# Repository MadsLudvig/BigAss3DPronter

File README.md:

# Industrial 3D Printer
*__Big 3D printer made with industrial parts from an injection molding machine__*

### Introduction

This is a 3D printer made with an extruder from an injection moulding machine and Motors and axis from several old ATM CNC robots. It will be using an material dryer and a mini vacuum conveyor for supplying the extruder with material. It will be build such that the extruder only moves on one axis because of its weight (approximately 50kg). The extruder will be moved on the x-axis and the bottom plate will be moved on the z- and y-axis. The software will be Marlin which is going to run on a Teensy 4.0. Then octoprint will be used as an Marlin host to control. Here octoprint will run on a Raspberry Pi 4.0 with an 15" industrial grade touch screen.

*__More information on the individual modules can be seen in the "Modules" folder__*

### Mechanical composition

Here as said before the extruder is going to be moved in the X-axis and the bottom plate is going to be moved in the Y- and Z-axis. This is seen in Figure 5 below:

*Figure 5: Here is seen an example of how the axis will look*

Here it should be noted that although the axis placements are correct on the image. The way the axisses are moved are not. This image is just to show axis placement. The Z-axis is not moving the extruder it should here be moving the bottom plate instead. The reason why the extruder is placed on the x-axis is because of its sheer size and weight. Here it will be advantagous only to move it from side to side to minimize movement of mass. To make the x-axis move the weight of the extruder, the long axis of the ATM CNC robot is going to be used. This is because this has lots of already built-in support and can therefore support the extruder with ease. It also has place for motor mounting, gear and gearrack for moving the axis, and a cable carrier. This i going to be very advantageus for running the material supply line for the extruder, motor cables for x and w axisses, and heating element wires for extruder. Everything will then be mounted on a steel frame made out of welded steel beams. The material of the bottom plate is being researched, so the best material can be found. For now the material is aluminium, but that could also be replaced with borosilicate glass because of its hardness and temperature resistance

### Global Bill of Materials

| Name                                         | Quantity |                             Link                             | Price (DKK) |
| :------------------------------------------- | :------: | :----------------------------------------------------------: | :---------: |
| Conradt mini vacuum conveyer                 |    1     |                                                              |    4000     |
| ILCE-QX1 Power adapter                       |    1     | [Link](https://www.subtel.dk/index.php?cl=details&offerId=3978956963&lang=6&anid=915664&cnid=192d2e4a1f71bd07ce1a5f9bbb185e09&campaign=dk-pla/Netzteil/915664&gclid=Cj0KCQiAs5eCBhCBARIsAEhk4r6M4nEBqRl9llAmq8cqiiVEmtkUiZZ6ZFrAzY_FEcEVpPGQpeQw50saAnzREALw_wcB) |     259     |
| 15" Touch screen                             |    1     | [Link](https://www.beetronics.dk/15-tommer-touchskaerm-metal-4-3) |    2699     |
| Cable                                        |    1     |   [Link](https://dk.rs-online.com/web/p/yy-kabel/1811780/)   |     589     |
| Connector                                    |    16    |  [Link](https://dk.rs-online.com/web/p/d-sub-stik/5443749/)  |    6.376    |
| Connector house                              |    16    | [Link](https://dk.rs-online.com/web/p/d-sub-bagkapper/5444039/) |    27.22    |
| Material dryer                               |    1     |                                                              |     NaN     |
| SN74LS640N                                   |    6     | [Link](https://www.ti.com/store/ti/en/p/product/?p=SN74LS640N) |    9.54     |
| SN74ABT245BN                                 |    6     | [Link](https://www.ti.com/store/ti/en/p/product/?p=SN74ABT245BN) |    4.52     |
| Aluminium bottom plate                       |    1     |                                                              |     NaN     |
| Heating elements bottom plate                |    1     |                                                              |     NaN     |
| Steel frame                                  |    1     |                                                              |     NaN     |
| Mounting adapter for servo motor to extruder |    1     |                                                              |     NaN     |

So here the price comes up to: 8169kr. DKK for now. Here it should be noted that this is not close to the final cost, since the mounting brackets, the steel frame, and the aluminium bottom plate will cost a lot.

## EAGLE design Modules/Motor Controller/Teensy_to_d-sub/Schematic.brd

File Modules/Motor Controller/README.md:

# Motor Controller
The motors are controlled by lenze servo controllers. All of the servo drives and the power management are already packed in a nice cabinet. This will be reused. Here the teensy will be sitting inside this cabinet. The model of the servo controllers is Lenze 9300. Here the X9 and X10 connectors will be used as seen here:

*Figure 1: Page 47 of lenze 9300 servodrive manual*

*__Lenze manual:  [BA_9300_Register_control_EN.pdf](/md_attachments/BA_9300_Register_control_EN.pdf)__*

Here the X9 connector is digital frequency input. This input requires a TTL encoder signal. Then the servo drive will mimic this encoder signal. This way the drive can be controlled. So the Teensy 4.0 will input the Marlin stepper signals to this input. The plan is to have 4 outputs on the teensy that, so the X,Y,Z,W axisses can be controlled. Here the W axis is the motor that turns the extruder. Another nice feature this allows is that the servo drives can easily be daisy chained if multiple motors is needed per axis by connecting the X10 and X9. 

To make connecting the inputs to the Teensy 4.0, a circuitboard is going to be made with 4 d-sub connectors. Here is the current state of the board drawing and schematic:

*Figure 2: Board*

*Figure 3: Here is seen a piece of the schematic*

As seen in figure 2, non-inverting- and inverting bus-trancievers are used to unload the teensy's output GPIO pins. The reason the inverting bus-trancievers are used is because the input signal is differential as seen in figure 1. 

The reason why the stepper output of Marlin can be connected directly to the TTL encoder signal of the X9 input is because the signals are identical as seen by comparing Figure 1 and Figure 4 below:

*Figure 4: Here is seen the stepper output marlin*

Here it should be noted that the Z signal is not necessary to use, so it will not be used. The z signal just signifies when the encoder has turned one revolution. This will not be relevant though since all stepping amounts will be calibrated in marlin at last.

#### The cable between X9 and X10

As seen in figure 1 there are specific requirements for the specific leaders in the cable that is going to run between x9 and x10. Here there have been chosen a 9-conductor cable at 0.5mm2. The connectors are going to be female-female, so there have been chosen some 9-pin d-sub connectors. The links for the parts can be seen in the BoM

### Bill of Materials

| Name                  | Quantity |                             Link                             | Price(DKK) |
| :-------------------- | :------: | :----------------------------------------------------------: | :--------: |
| Cable                 |    1     |   [Link](https://dk.rs-online.com/web/p/yy-kabel/1811780/)   |    589     |
| D-sub Connector       |    16    |  [Link](https://dk.rs-online.com/web/p/d-sub-stik/5443749/)  |   6.376    |
| D-sub Connector house |    16    | [Link](https://dk.rs-online.com/web/p/d-sub-bagkapper/5444039/) |   27.22    |
| SN74LS640N            |    6     | [Link](https://www.ti.com/store/ti/en/p/product/?p=SN74LS640N) |    9.54    |
| SN74ABT245BN          |    6     | [Link](https://www.ti.com/store/ti/en/p/product/?p=SN74ABT245BN) |    4.52    |

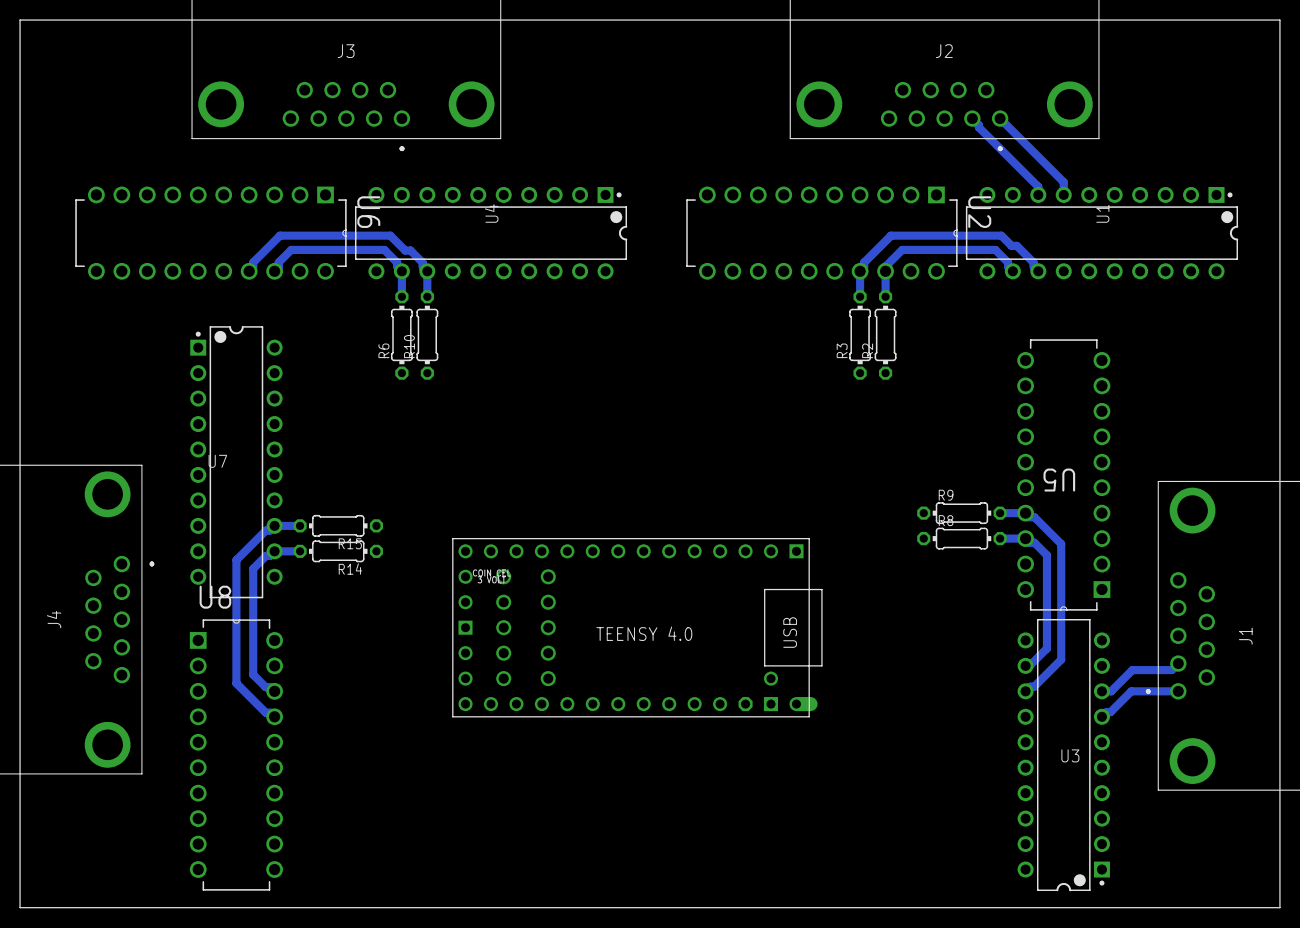
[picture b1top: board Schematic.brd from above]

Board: 2 copper layers, 125.7 x 88.6 mm, 21 parts (0 on the bottom side), 34 nets.

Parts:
J1, J2, J3, J4: 182-009-113R531; 182009113R531
R2, R3, R6, R8, R9, R10, R14, R15: 400; 0204/7
U1, U3, U4, U7: TEXAS_INSTRUMENTS_SN54LS245TEXAS_INSTRUMENTS_SN54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; TEXAS_INSTRUMENTS_SN54LS245_0
U2, U5, U6, U8: SN74LS640N; DIP254P762X508-20
U$1: TEENSY40

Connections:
+5V: U1.20, U2.20, U3.20, U4.20, U5.20, U6.20, U7.20, U8.20, U$1.VIN
/A1: J1.2, U5.2
/A2: J2.2, U2.2
/A3: J3.2, U6.2
/A4: J4.2, U8.2
/B1: J1.9, U5.3
/B2: J2.9, U2.3
/B3: J3.9, U6.3
/B4: J4.9, U8.3
A1: J1.3, U3.8
A2: J2.3, U1.8
A3: J3.3, U4.8
A4: J4.3, U7.8
B1: J1.1, U3.7
B2: J2.1, U1.7
B3: J3.1, U4.7
B4: J4.1, U7.7
GND: J1.5, J2.5, J3.5, J4.5, U1.1, U1.10, U1.14, U1.15, U1.16, U1.17, U1.18, U1.19, U2.1, U2.10, U2.11, U2.12, U2.13, U2.14, U2.15, U2.19, U3.1, U3.10, U3.14, U3.15, U3.16, U3.17, U3.18, U3.19, U4.1, U4.10, U4.14, U4.15, U4.16, U4.17, U4.18, U4.19, U5.1, U5.10, U5.11, U5.12, U5.13, U5.14, U5.15, U5.19, U6.1, U6.10, U6.11, U6.12, U6.13, U6.14, U6.15, U6.19, U7.1, U7.10, U7.14, U7.15, U7.16, U7.17, U7.18, U7.19, U8.1, U8.10, U8.11, U8.12, U8.13, U8.14, U8.15, U8.19, U$1.GND2
IA1: R8.2, U3.12, U5.18
IA2: R2.2, U1.12, U2.18
IA3: R6.2, U4.12, U6.18
IA4: R14.2, U7.12, U8.18
IB1: R9.2, U3.13, U5.17
IB2: R3.2, U1.13, U2.17
IB3: R10.2, U4.13, U6.17
IB4: R15.2, U7.13, U8.17
JA1: R8.1, U$1.1-TX1
JA2: R2.1, U$1.4-BCLK2
JA3: R6.1, U$1.7-RX2/OUT1A
JA4: R14.1, U$1.10-CS/MQSR
JB1: R9.1, U$1.0-RX1
JB2: R3.1, U$1.3-LRCLK2
JB3: R10.1, U$1.6-OUT1D
JB4: R15.1, U$1.9-OUT1C

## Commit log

2021-03-08 Added Eagle files
2021-03-10 Organised with modules folder
2021-03-12 Added marlin firmware
